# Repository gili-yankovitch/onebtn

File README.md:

# OneBtn
This is the OneBtn. A context-aware multi-purpose macro pad to control everything with  a push of a (single) button.

## Prerequisits
### Software
Please install the following software to be able to flash software to the device:
* [Arduino SDK](https://www.arduino.cc/en/software)
* [Platformio](https://platformio.org/install/cli) or VScode with Platformio AddOn

### Hardware
All PCB specs are provided here under [hardware/](https://github.com/gili-yankovitch/onebtn/tree/master/hardware). This can be easily manufactured as well as paneled for a larger volume. There are no special requirements for this board's manufacturing process.

#### Bill of Materials
| Quantity | Component Description | Mfr. No | Datasheet |
|----------|-----------------------|---------|-----------|
| 2 | SMD 1/4W 22 OHM 1% | RK73H2ATTD22R0F | [Datasheet](https://www.mouser.co.il/datasheet/2/219/RK73H-1825326.pdf) |
| 1 | SMD 1 kOhms 125 mW 0805 5% | RC0805JR-071KL | [Datasheet](https://www.mouser.co.il/datasheet/2/447/PYu_RC_Group_51_RoHS_L_11-1984063.pdf) |
| 1 | SMD 1/4watts 10Kohms 5% | RK73B2ATTD103J | [Datasheet](https://www.mouser.co.il/datasheet/2/219/RK73B-1825463.pdf) |
| 1 | SMD 1M ohm 1% 50 ppm Thin Film | RT0805FRE101ML | [Datasheet](https://www.mouser.co.il/datasheet/2/447/PYu_RT_1_to_0_01_RoHS_L_12-3003070.pdf) |
| 1 | SMD/SMT 100V 20pF C0G 0805 5% | CC0805JRNPO0BN200 | [Datasheet](https://www.mouser.co.il/datasheet/2/447/UPY_NP0X7R_MV_100_to_630V_24-2604388.pdf) |
| 1 | SMD/SMT CAP ,MLCC ,0805,25V ,X7R,1.0UF20% ,T&R | MCAST21GSB7105MTNB25 | [Datasheet](https://www.mouser.co.il/datasheet/2/396/Taiyo_Yuden_1102023_MC_mlcc_all_e-3081584.pdf) |
| 1 | SMD/SMT 50V 0.1uF X7R 0805 10% | C0805C104K5RAC7411 | [Datasheet](https://www.mouser.co.il/datasheet/2/212/KEM_C1002_X7R_SMD-1102033.pdf) |
| 1 | Type C 16Pins SMT Socket Connector USB 3.1 Type-C Female MD DIP | [Link](https://www.aliexpress.com/item/4001076043694.html?spm=a2g0o.order_list.0.0.2e2f1802zEBigU) | [Datasheet](https://ae01.alicdn.com/kf/H1e697b3dd3c54072b04ede95a2d44105H.jpg) |
| 1 | 0.2W Intelligent external control surface mount SMD LED | SK6812Mini-E | [Datasheet](https://cdn-shop.adafruit.com/product-files/4960/4960_SK6812MINI-E_REV02_EN.pdf) |
| 1 | Crystals Crystals 16MHz 20pF | FOXSDLF/160-20 | [Datasheet](https://www.mouser.co.il/datasheet/2/3/C4SD-2141100.pdf) |
| 1 | 8-bit Microcontrollers - MCU 8-bit Microcontrollers - MCU AVR USB 32K FLASH | ATMEGA32U4-AU | [Datasheet](https://www.mouser.co.il/datasheet/2/268/Atmel_7766_8_bit_AVR_ATmega16U4_32U4_Datasheet-1315135.pdf) |
| 1 | OLED Display LCD 0.42" White LCD Screen Display Module | [Link](https://www.aliexpress.com/item/1005004674483621.html?spm=a2g0o.order_list.order_list_main.53.3f8418028cM6Vv) | [Datasheet](https://www.vishay.com/docs/37902/oled128o064dbpp3n00000.pdf) |
| 1 | Transparent Cover Key Keycaps Double-layer Custom Switch | [Link](https://www.aliexpress.com/item/1005002716375572.html?spm=a2g0o.order_list.order_list_main.137.3f8418028cM6Vv) |  |
| 1 | Outemu Switch Mechanical Keyboard Switch 3Pin | [Link](https://www.aliexpress.com/item/1005002378701948.html?spm=a2g0o.order_list.order_list_main.242.3f8418028cM6Vv) |  |

# Software
## Building
To build this project, usage of PlatformIO is recommended although the Arduino IDE will probably work as well. To use PlatformIO, simply run:
```
pio run --environment leonardo
```

## Flashing
This device accepts software in two ways: First through the ICSP port and the other through USB (after flashing Arduino Leonardo bootloader).

To flash using the ICSP port, simply use any Arduino device, flash it with the Arduino as ISP example from the Arduino IDE and use it to flash firmware to this device. While doing that, one might wish to use the Arduino IDE further by simply flashing the Arduino Bootloader to the device. Once this is done, USB flashing will be available. To flash the software using USB, simply run:
```
pio run --environment leonardo --target upload
```

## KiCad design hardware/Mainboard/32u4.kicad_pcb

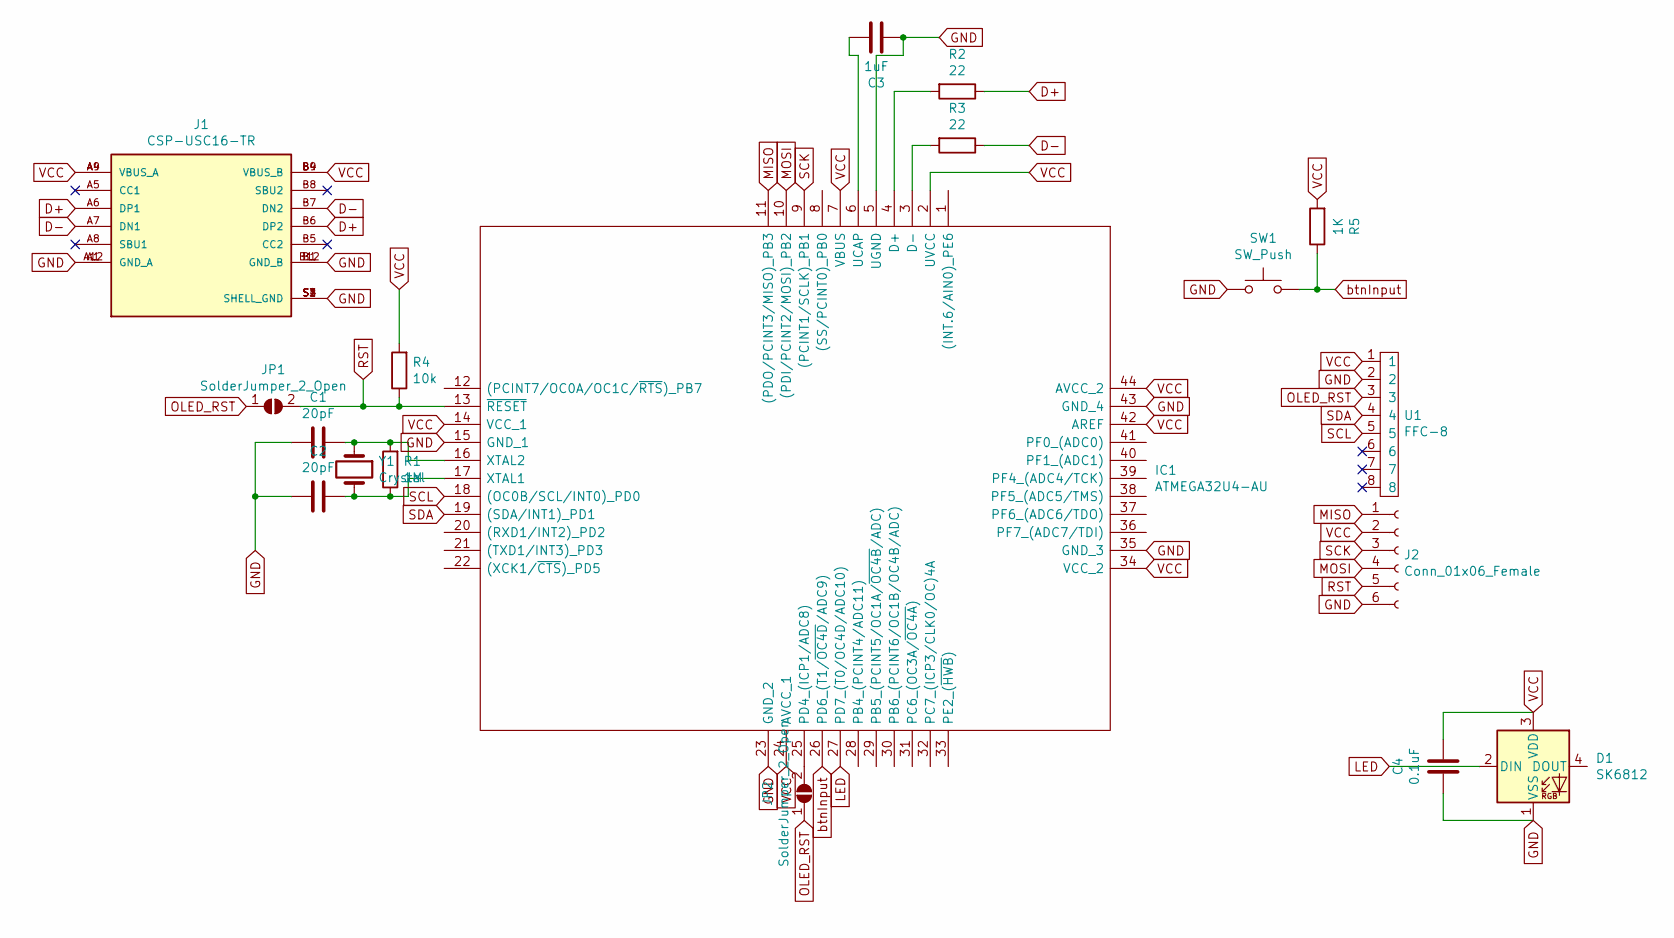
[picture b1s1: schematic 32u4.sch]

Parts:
C1, C2: 20pF; C_0805_2012Metric_Pad1.18x1.45mm_HandSolder
C3: 1uF; C_0805_2012Metric_Pad1.18x1.45mm_HandSolder
C4: 0.1uF; C_0805_2012Metric_Pad1.18x1.45mm_HandSolder
D1: SK6812; LED-3535
IC1: ATMEGA32U4-AU; QFP80P1200X1200X120-44N; Mouser Part Number 556-ATMEGA32U4-AU
J1: CSP-USC16-TR; VALCON_CSP-USC16-TR-Fixed; PARTREV A0
J2: Conn_01x06_Female; PinSocket_2x03_P2.54mm_Vertical
JP1, JP2: SolderJumper_2_Open; SolderJumper-2_P1.3mm_Open_RoundedPad1.0x1.5mm
R1: 1M; R_0805_2012Metric_Pad1.20x1.40mm_HandSolder
R2, R3: 22; R_0805_2012Metric_Pad1.20x1.40mm_HandSolder
R4: 10k; R_0805_2012Metric_Pad1.20x1.40mm_HandSolder
R5: 1K; R_0805_2012Metric_Pad1.20x1.40mm_HandSolder
SW1: SW_Push; SW_Cherry_MX_1.00u_PCB
U1: FFC-8; OLED-0.6Pitch-8Pins
Y1: Crystal; FOXSLF16020

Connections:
D+: J1.A6 (DP1), J1.B6 (DP2), R2.1
D-: J1.A7 (DN1), J1.B7 (DN2), R3.1
GND: C1.2, C2.2, C3.2, C4.2, D1.1 (VSS), IC1.5 (UGND), IC1.15 (GND_1), IC1.23 (GND_2), IC1.35 (GND_3), IC1.43 (GND_4), J1.A1 (GND_A), J1.A12 (GND_A), J1.B1 (GND_B), J1.B12 (GND_B), J1.S1 (SHELL_GND), J1.S2 (SHELL_GND), J1.S3 (SHELL_GND), J1.S4 (SHELL_GND), J2.6, SW1.1, U1.2
LED: D1.2 (DIN), IC1.27 (PD7_(T0/OC4D/ADC10))
MISO: IC1.11 ((PDO/PCINT3/MISO)_PB3), J2.1
MOSI: IC1.10 ((PDI/PCINT2/MOSI)_PB2), J2.4
unnamed: C1.1, IC1.16 (XTAL2), R1.2, Y1.1
unnamed: C2.1, IC1.17 (XTAL1), R1.1, Y1.2
unnamed: C3.1, IC1.6 (UCAP)
unnamed: IC1.3 (D-), R3.2
unnamed: IC1.4 (D+), R2.2
unnamed: IC1.25 (PD4_(ICP1/ADC8)), JP2.2 (B)
OLED_RST: JP1.1 (A), JP2.1 (A), U1.3
RST: IC1.13 (~RESET), J2.5, JP1.2 (B), R4.1
SCK: IC1.9 ((PCINT1/SCLK)_PB1), J2.3
SCL: IC1.18 ((OC0B/SCL/INT0)_PD0), U1.5
SDA: IC1.19 ((SDA/INT1)_PD1), U1.4
VCC: C4.1, D1.3 (VDD), IC1.2 (UVCC), IC1.7 (VBUS), IC1.14 (VCC_1), IC1.24 (AVCC_1), IC1.34 (VCC_2), IC1.42 (AREF), IC1.44 (AVCC_2), J1.A4 (VBUS_A), J1.A9 (VBUS_A), J1.B4 (VBUS_B), J1.B9 (VBUS_B), J2.2, R4.2, R5.2, U1.1
btnInput: IC1.26 (PD6_(T1/~OC4D~/ADC9)), R5.1, SW1.2

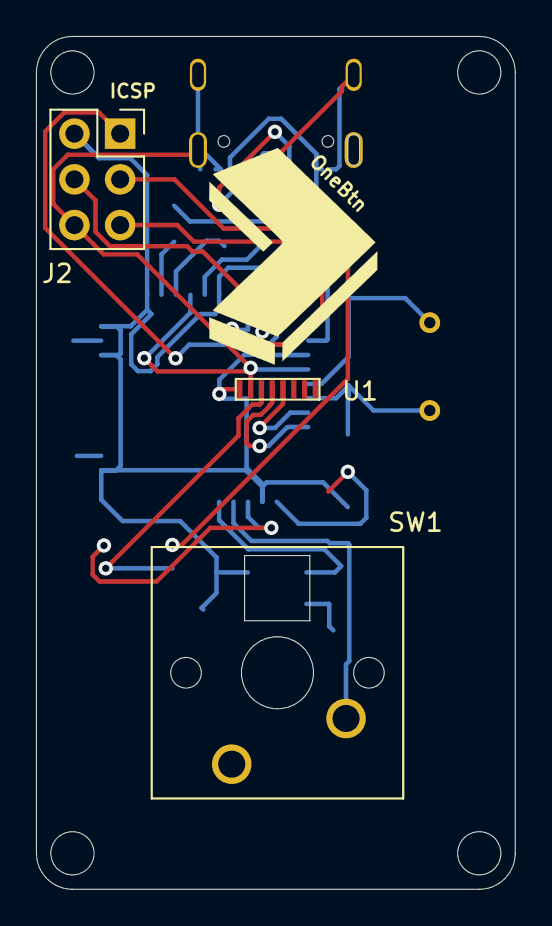
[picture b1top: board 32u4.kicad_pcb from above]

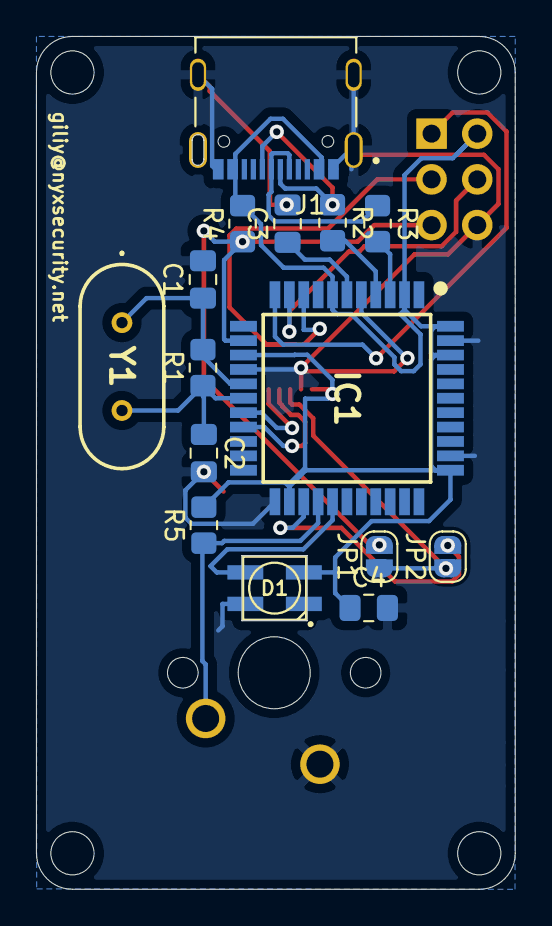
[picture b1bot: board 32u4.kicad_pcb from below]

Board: 2 copper layers, 26.6 x 47.4 mm, 18 parts (15 on the bottom side), 19 nets.

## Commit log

2023-04-06 WIP automatic window detection + key switching
2023-04-06 Fixing key code bug
2023-04-06 Adding config examples
2023-04-06 Adding title detection + relative config location
2023-04-07 Support on-the-fly config change and making presses work smoother
2023-04-25 Adding hardware source files
2023-05-05 Adding readme and a bunch of small changes to config
